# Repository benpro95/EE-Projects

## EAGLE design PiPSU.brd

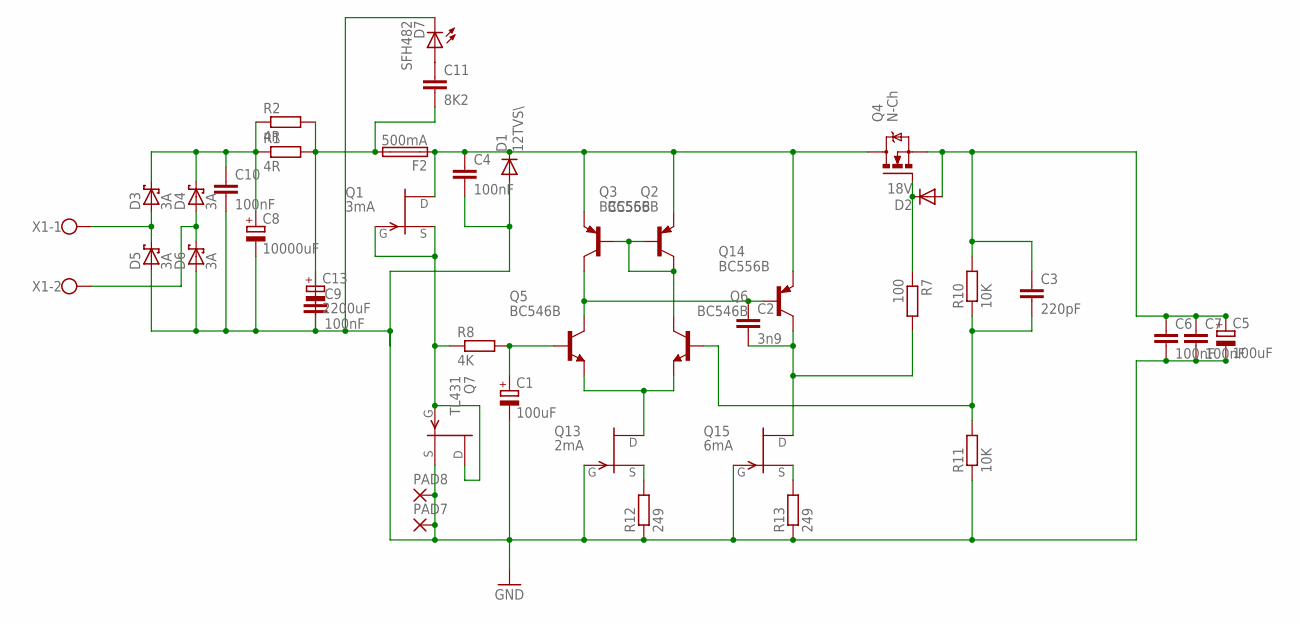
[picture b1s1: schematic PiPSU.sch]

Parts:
C1, C5: 100uF; E3,5-8
C2: 3n9; C1210K
C3: 220pF; C1210
C4, C6, C7, C10: 100nF; C1210
C8: 10000uF; E7,5-18
C9: 100nF; C102-043X133
C11: 8K2; C1210
C13: 2200uF; E7,5-18
D1: 12TVS\; DO35-10
D2: 18V; DO35-7
D3, D4, D5, D6: 3A; SMC
D7: SFH482
F2: 500mA; 19560
PAD7, PAD8: 3,81/1,4
Q1: 3mA; TO92-
Q2, Q3, Q14: BC556B; TO92-EBC
Q4: N-Ch; TO-247AD-H
Q5, Q6: BC546B; TO92-EBC
Q7: TL431; TO92-
Q13: 2mA; TO92-
Q15: 6mA; TO92-
R1, R2: 4R; 0309/12
R7: 100; 0309/12
R8: 4K; 0309/12
R10, R11: 10K; R1210
R12, R13: 249; R1210
X1: W237-102; MPN 237-102

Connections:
FGD: C1.-, C4.2, C5.-, C6.2, C7.2, C8.-, C9.2, C10.2, C13.-, D1.A, D5.A, D6.A, D7.K (C), PAD7.1, PAD8.1, Q7.2 (S), Q13.1 (G), Q15.1 (G), R11.1, R12.1, R13.1
unnamed: C9.1, C11.2, C13.+, F2.2, R1.2, R2.2
unnamed: C8.+, C10.1, D3.C, D4.C, R1.1, R2.1
unnamed: D3.A, D5.C, X1.1
unnamed: D4.A, D6.C, X1.2
unnamed: C3.1, C5.+, C6.1, C7.1, D2.A, Q4.S, R10.2
unnamed: C4.1, D1.C, F2.1, Q1.3 (D), Q2.E, Q3.E, Q4.D, Q14.E
unnamed: C11.1, D7.A
unnamed: D2.C, Q4.G, R7.1
unnamed: C1.+, Q5.B, R8.2
unnamed: Q2.B, Q3.B, Q3.C, Q6.C
unnamed: Q5.E, Q6.E, Q13.3 (D)
unnamed: C2.1, Q2.C, Q5.C, Q14.B
unnamed: C2.2, Q14.C, Q15.3 (D), R7.2
unnamed: C3.2, Q6.B, R10.1, R11.2
unnamed: Q1.1 (G), Q1.2 (S), Q7.1 (G), Q7.3 (D), R8.1
unnamed: Q13.2 (S), R12.2
unnamed: Q15.2 (S), R13.2

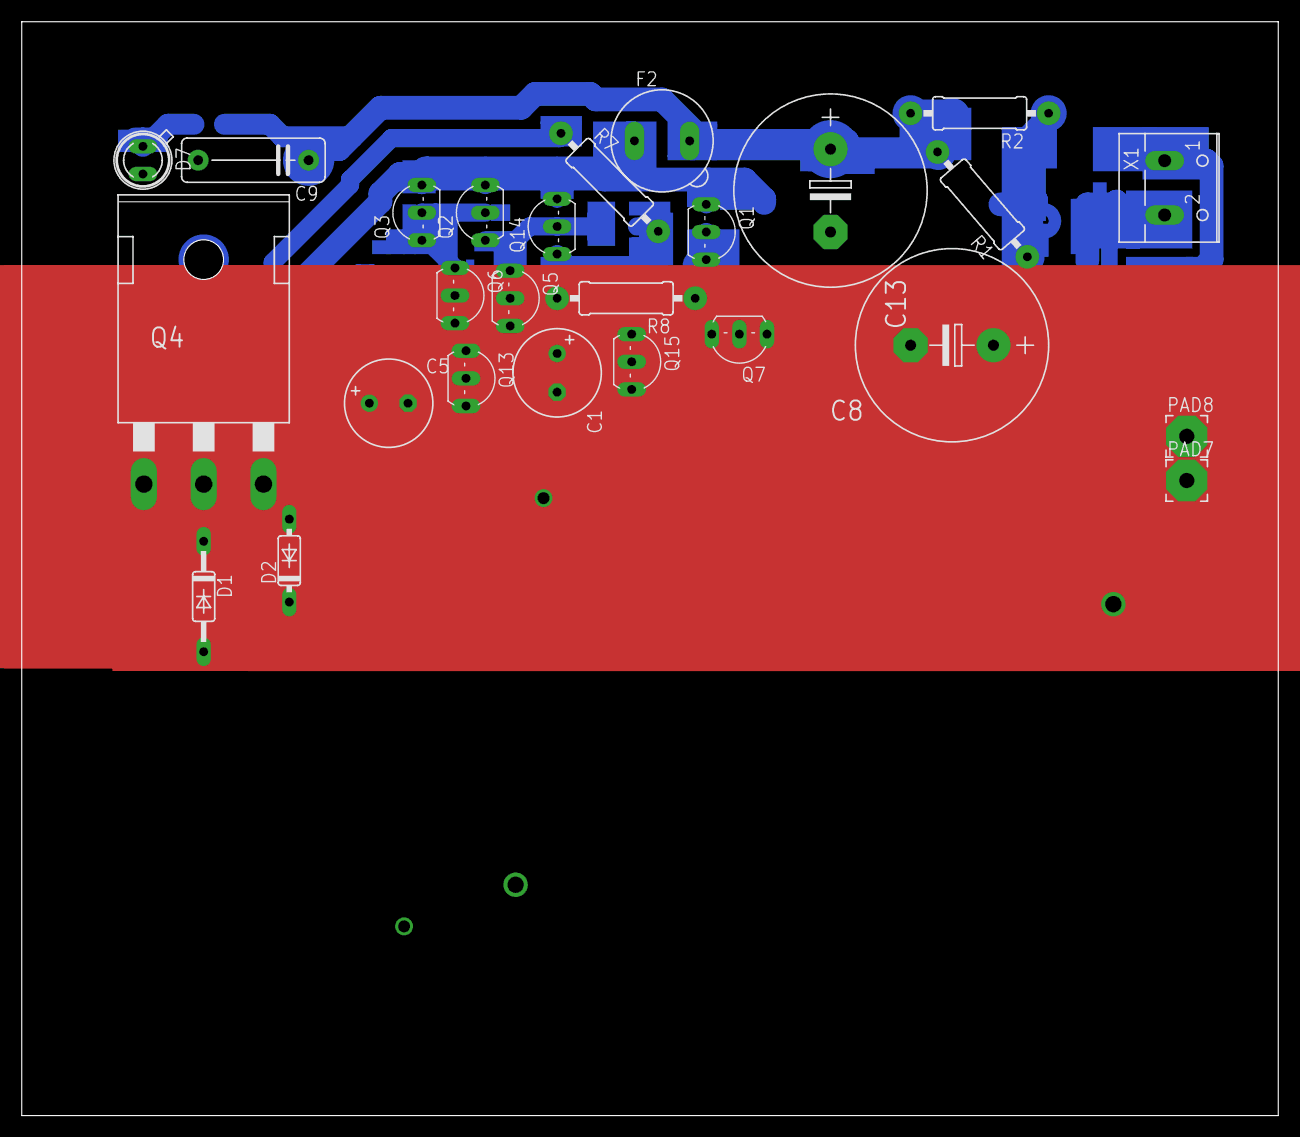
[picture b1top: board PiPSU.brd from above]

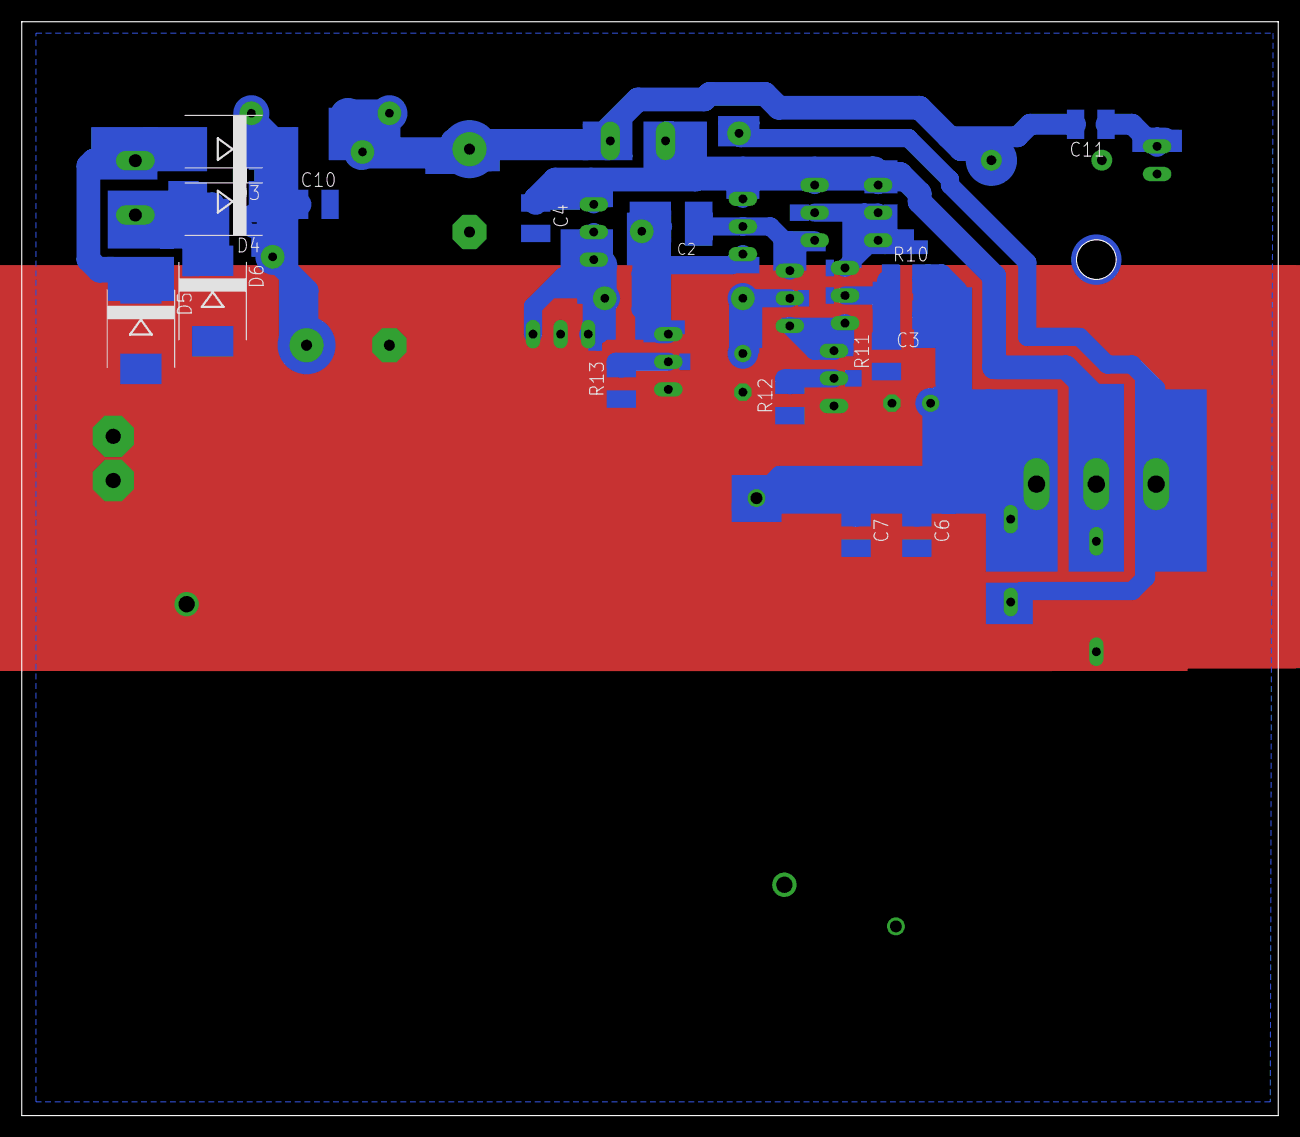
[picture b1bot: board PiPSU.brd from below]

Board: 2 copper layers, 115.6 x 100.6 mm, 41 parts (15 on the bottom side), 18 nets.
